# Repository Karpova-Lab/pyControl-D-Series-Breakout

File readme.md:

- View documentation at  https://karpova-lab.github.io/pyControl-D-Series-Breakout/
- Ask questions at https://github.com/Karpova-Lab/pyControl-D-series-Breakout/discussions
- Clone repository from https://github.com/Karpova-Lab/pyControl-D-Series-Breakout

## License
This project is licensed under the [Janelia open-source hardware license](license_hardare.txt) and [Janelia 3-term BSD open-source software license](license_software.txt).

Please contact [innovation@janelia.hhmi.org](mailto:innovation@janelia.hhmi.org) if you have any questions about licensing or would like to use this project commercially.

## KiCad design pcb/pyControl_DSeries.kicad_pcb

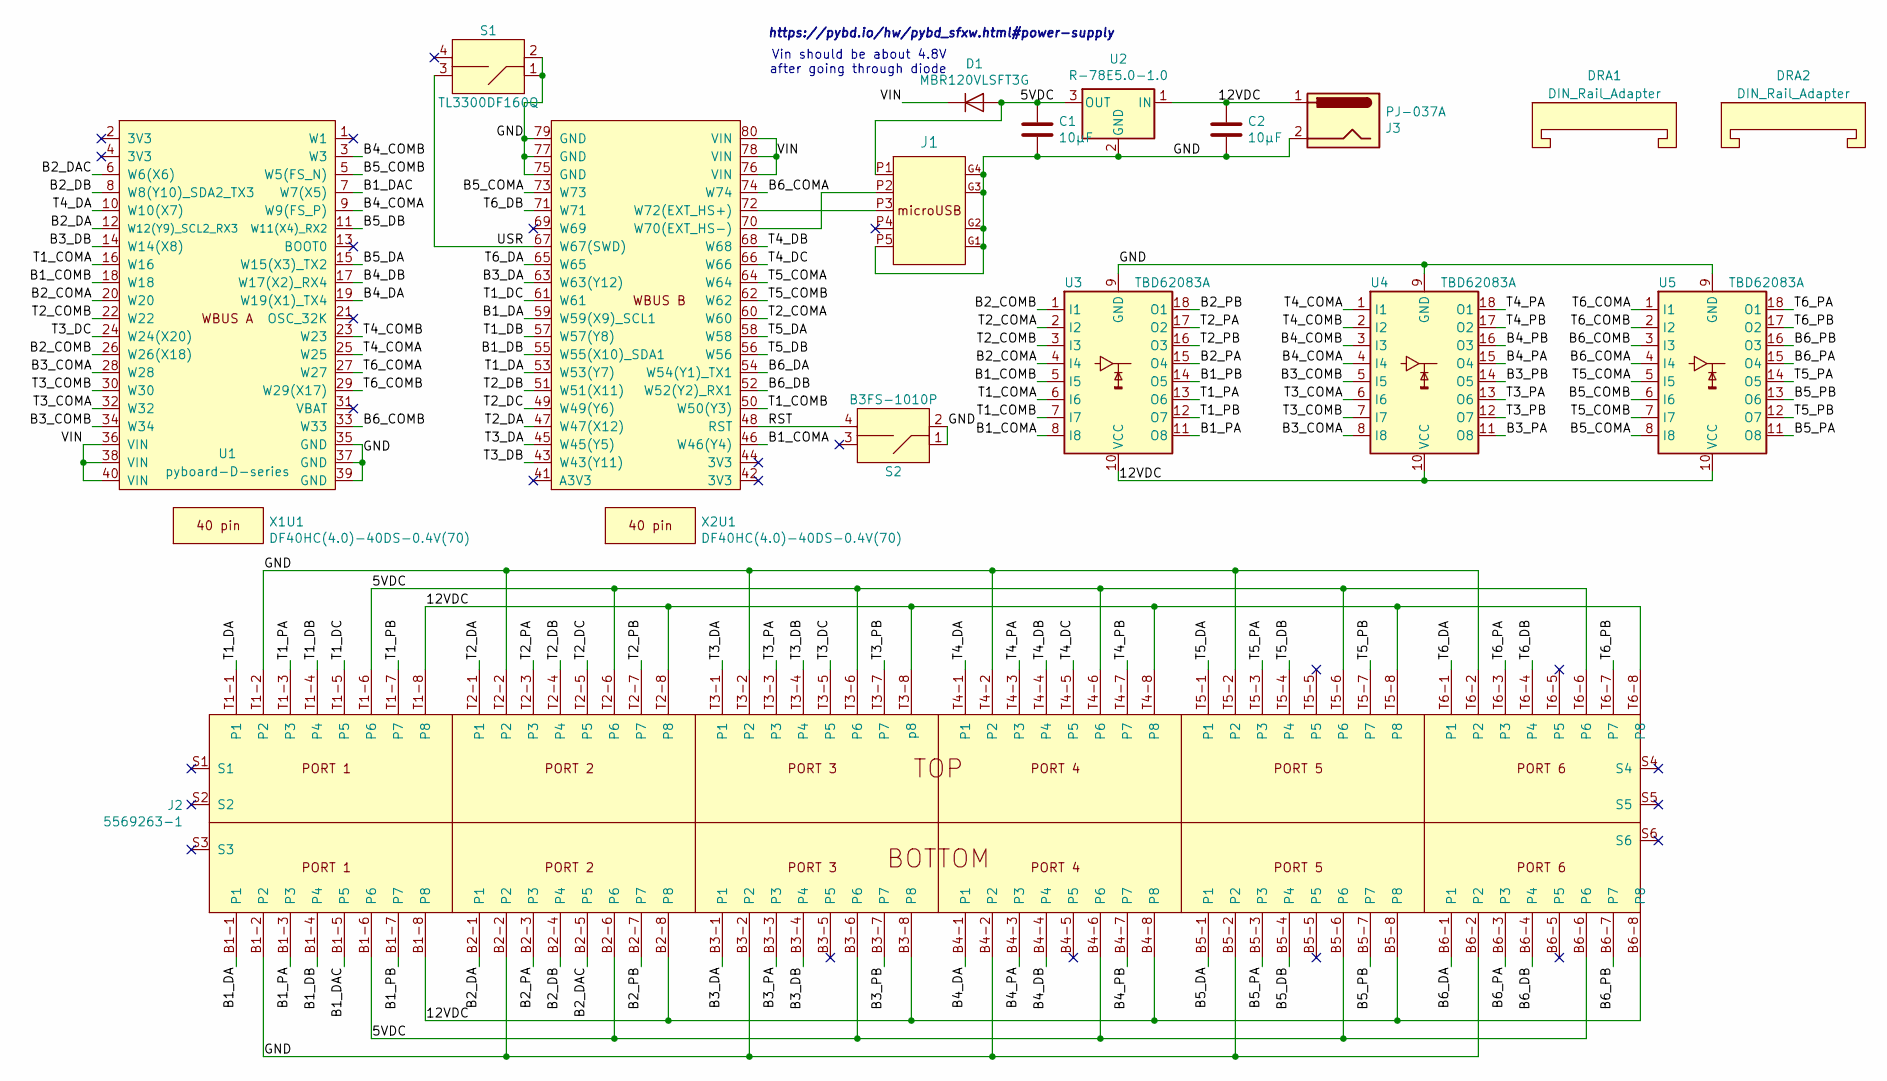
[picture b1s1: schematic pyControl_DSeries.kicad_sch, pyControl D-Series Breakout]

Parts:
C1, C2: 10µF; C_1206_3216Metric
D1: MBR120VLSFT3G; D_SOD-123F
DRA1, DRA2: DIN_Rail_Adapter; DIN_Clip
J1: 10118194-0001LF; microUSB_horizontal_socket
J2: 5569263-1; RJ45_12Port
J3: PJ-037A; DC_Jack
S1: TL3300DF160Q; 12mm_tactile_smd
S2: B3FS-1010P; 6mm_tactile_smd
U1: pyboard-D-series; PyBoard_D-Series
U2: R-78E5.0-1.0; Converter_DCDC_RECOM_R-78E-0.5_THT
U3, U4, U5: TBD62083A; SSOP-18_4.4x6.5mm_P0.65mm
X1U1, X2U1: DF40HC(4.0)-40DS-0.4V(70); Hirose_40_pin

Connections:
/5VDC: C1.1, D1.2 (A), J1.P1, J2.B1-6 (P6), J2.B2-6 (P6), J2.B3-6 (P6), J2.B4-6 (P6), J2.B5-6 (P6), J2.B6-6 (P6), J2.T1-6 (P6), J2.T2-6 (P6), J2.T3-6 (P6), J2.T4-6 (P6), J2.T5-6 (P6), J2.T6-6 (P6), U2.3 (OUT)
/12VDC: C2.1, J2.B1-8 (P8), J2.B2-8 (P8), J2.B3-8 (P8), J2.B4-8 (P8), J2.B5-8 (P8), J2.B6-8 (P8), J2.T1-8 (P8), J2.T2-8 (P8), J2.T3-8 (p8), J2.T4-8 (P8), J2.T5-8 (P8), J2.T6-8 (P8), J3.1, U2.1 (IN), U3.10 (VCC), U4.10 (VCC), U5.10 (VCC)
/B1_COMA: U1.46 (W46(Y4)), U3.8 (I8)
/B1_COMB: U1.18 (W18), U3.5 (I5)
/B1_DA: J2.B1-1 (P1), U1.59 (W59(X9)_SCL1)
/B1_DAC: J2.B1-5 (P5), U1.7 (W7(X5))
/B1_DB: J2.B1-4 (P4), U1.55 (W55(X10)_SDA1)
/B1_PA: J2.B1-3 (P3), U3.11 (O8)
/B1_PB: J2.B1-7 (P7), U3.14 (O5)
/B2_COMA: U1.20 (W20), U3.4 (I4)
/B2_COMB: U1.26 (W26(X18)), U3.1 (I1)
/B2_DA: J2.B2-1 (P1), U1.12 (W12(Y9)_SCL2_RX3)
/B2_DAC: J2.B2-5 (P5), U1.6 (W6(X6))
/B2_DB: J2.B2-4 (P4), U1.8 (W8(Y10)_SDA2_TX3)
/B2_PA: J2.B2-3 (P3), U3.15 (O4)
/B2_PB: J2.B2-7 (P7), U3.18 (O1)
/B3_COMA: U1.28 (W28), U4.8 (I8)
/B3_COMB: U1.34 (W34), U4.5 (I5)
/B3_DA: J2.B3-1 (P1), U1.63 (W63(Y12))
/B3_DB: J2.B3-4 (P4), U1.14 (W14(X8))
/B3_PA: J2.B3-3 (P3), U4.11 (O8)
/B3_PB: J2.B3-7 (P7), U4.14 (O5)
/B4_COMA: U1.9 (W9(FS_P)), U4.4 (I4)
/B4_COMB: U1.3 (W3), U4.3 (I3)
/B4_DA: J2.B4-1 (P1), U1.19 (W19(X1)_TX4)
/B4_DB: J2.B4-4 (P4), U1.17 (W17(X2)_RX4)
/B4_PA: J2.B4-3 (P3), U4.15 (O4)
/B4_PB: J2.B4-7 (P7), U4.16 (O3)
/B5_COMA: U1.73 (W73), U5.8 (I8)
/B5_COMB: U1.5 (W5(FS_N)), U5.6 (I6)
/B5_DA: J2.B5-1 (P1), U1.15 (W15(X3)_TX2)
/B5_DB: J2.B5-4 (P4), U1.11 (W11(X4)_RX2)
/B5_PA: J2.B5-3 (P3), U5.11 (O8)
/B5_PB: J2.B5-7 (P7), U5.13 (O6)
/B6_COMA: U1.74 (W74), U5.4 (I4)
/B6_COMB: U1.33 (W33), U5.3 (I3)
/B6_DA: J2.B6-1 (P1), U1.54 (W54(Y1)_TX1)
/B6_DB: J2.B6-4 (P4), U1.52 (W52(Y2)_RX1)
/B6_PA: J2.B6-3 (P3), U5.15 (O4)
/B6_PB: J2.B6-7 (P7), U5.16 (O3)
/GND: C1.2, C2.2, J1.G1, J1.G2, J1.G3, J1.G4, J1.P5, J2.B1-2 (P2), J2.B2-2 (P2), J2.B3-2 (P2), J2.B4-2 (P2), J2.B5-2 (P2), J2.B6-2 (P2), J2.T1-2 (P2), J2.T2-2 (P2), J2.T3-2 (P2), J2.T4-2 (P2), J2.T5-2 (P2), J2.T6-2 (P2), J3.2, S1.1 (in1), S1.2 (in2), S2.1 (in1), S2.2 (in2), U1.35 (GND), U1.37 (GND), U1.39 (GND), U1.75 (GND), U1.77 (GND), U1.79 (GND), U2.2 (GND), U3.9 (GND), U4.9 (GND), U5.9 (GND)
/RST: S2.4 (out2), U1.48 (RST)
/T1_COMA: U1.16 (W16), U3.6 (I6)
/T1_COMB: U1.50 (W50(Y3)), U3.7 (I7)
/T1_DA: J2.T1-1 (P1), U1.53 (W53(Y7))
/T1_DB: J2.T1-4 (P4), U1.57 (W57(Y8))
/T1_DC: J2.T1-5 (P5), U1.61 (W61)
/T1_PA: J2.T1-3 (P3), U3.13 (O6)
/T1_PB: J2.T1-7 (P7), U3.12 (O7)
/T2_COMA: U1.60 (W60), U3.2 (I2)
/T2_COMB: U1.22 (W22), U3.3 (I3)
/T2_DA: J2.T2-1 (P1), U1.47 (W47(X12))
/T2_DB: J2.T2-4 (P4), U1.51 (W51(X11))
/T2_DC: J2.T2-5 (P5), U1.49 (W49(Y6))
/T2_PA: J2.T2-3 (P3), U3.17 (O2)
/T2_PB: J2.T2-7 (P7), U3.16 (O3)
/T3_COMA: U1.32 (W32), U4.6 (I6)
/T3_COMB: U1.30 (W30), U4.7 (I7)
/T3_DA: J2.T3-1 (P1), U1.45 (W45(Y5))
/T3_DB: J2.T3-4 (P4), U1.43 (W43(Y11))
/T3_DC: J2.T3-5 (P5), U1.24 (W24(X20))
/T3_PA: J2.T3-3 (P3), U4.13 (O6)
/T3_PB: J2.T3-7 (P7), U4.12 (O7)
/T4_COMA: U1.25 (W25), U4.1 (I1)
/T4_COMB: U1.23 (W23), U4.2 (I2)
/T4_DA: J2.T4-1 (P1), U1.10 (W10(X7))
/T4_DB: J2.T4-4 (P4), U1.68 (W68)
/T4_DC: J2.T4-5 (P5), U1.66 (W66)
/T4_PA: J2.T4-3 (P3), U4.18 (O1)
/T4_PB: J2.T4-7 (P7), U4.17 (O2)
/T5_COMA: U1.64 (W64), U5.5 (I5)
/T5_COMB: U1.62 (W62), U5.7 (I7)
/T5_DA: J2.T5-1 (P1), U1.58 (W58)
/T5_DB: J2.T5-4 (P4), U1.56 (W56)
/T5_PA: J2.T5-3 (P3), U5.14 (O5)
/T5_PB: J2.T5-7 (P7), U5.12 (O7)
/T6_COMA: U1.27 (W27), U5.1 (I1)
/T6_COMB: U1.29 (W29(X17)), U5.2 (I2)
/T6_DA: J2.T6-1 (P1), U1.65 (W65)
/T6_DB: J2.T6-4 (P4), U1.71 (W71)
/T6_PA: J2.T6-3 (P3), U5.18 (O1)
/T6_PB: J2.T6-7 (P7), U5.17 (O2)
/USR: S1.3 (out1), U1.67 (W67(SWD))
/VIN: D1.1 (K), U1.36 (VIN), U1.38 (VIN), U1.40 (VIN), U1.76 (VIN), U1.78 (VIN), U1.80 (VIN)
unnamed: J1.P2, U1.70 (W70(EXT_HS-))
unnamed: J1.P3, U1.72 (W72(EXT_HS+))

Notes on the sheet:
https://pybd.io/hw/pybd_sfxw.html#power-supply
Vin should be about 4.8V after going through diode

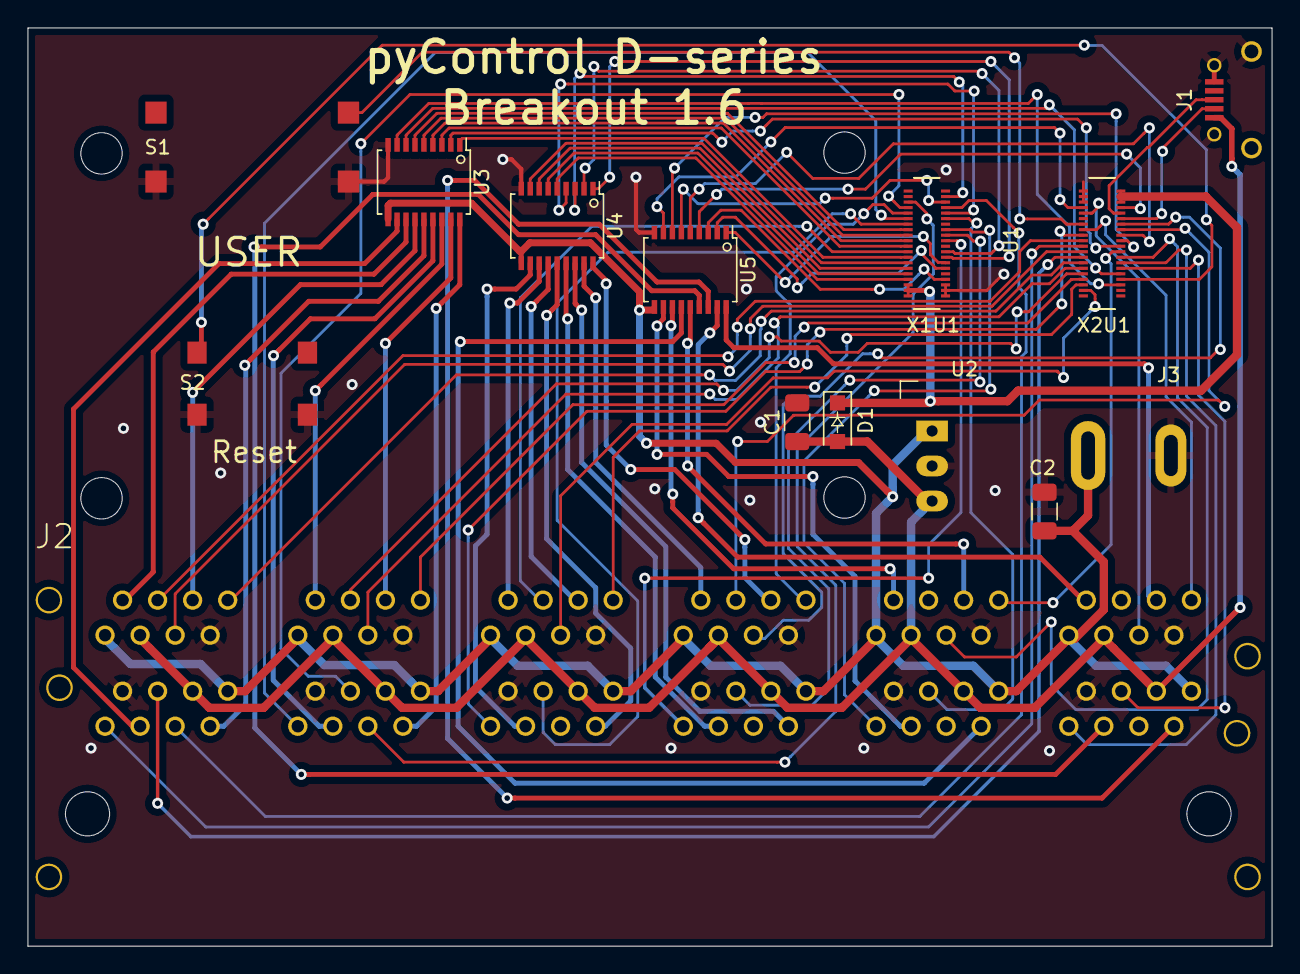
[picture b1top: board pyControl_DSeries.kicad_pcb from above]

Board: 2 copper layers, 90.2 x 66.5 mm, 17 parts (0 on the bottom side), 86 nets.

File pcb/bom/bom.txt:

"Qty","Reference","Description","Value/MPN","Purchase Link"
"2","C2, C1","1206 Capacitor","10µF","https://www.digikey.com/products/en?keywords=1276-1804-1-ND"
"1","D1","Schottky Diode","MBR120VLSFT3G","https://www.digikey.com/products/en?keywords=MBR120VLSFT3GOSCT-ND"
"1","J1","Micro USB Socket","10118194-0001LF","https://www.digikey.com/products/en?keywords=609-4618-1-ND"
"1","J2","12-port RJ45 Connector","5569263-1","https://www.digikey.com/products/en?keywords=5569263"
"1","J3","Barrel Jack Connector","PJ-037A","https://www.digikey.com/product-detail/en/cui-inc/PJ-037A/CP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"
"1","S1","Large Tactile Switch","TL3300DF160Q","https://www.digikey.com/products/en?keywords=EG4906CT-ND"
"1","S2","Small Tactile Switch","B3FS-1010P","https://www.digikey.com/products/en?keywords=sw1440ct"
"1","U2","5V DC to DC Converter","R-78E5.0-1.0","https://www.digikey.com/products/en?keywords=945-2201-ND"
"3","U5, U4, U3","8-channel Driver Array","TBD62083A","https://www.digikey.com/products/en?keywords=TBD62083AFNGELCT-ND"
"2","X2U1, X1U1","40-pin Connector","DF40HC(4.0)-40DS-0.4V(70)","https://www.digikey.com/products/en?keywords=H124604CT-ND"

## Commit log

2019-04-12 Initial commit. v1.0
2019-04-24 rev 1.1 fixed pins on dc jack and linear regulator. connected T3_DC repositioned DIN adapters added BOM and datasheets
2019-05-07 made footprint and symbol libraries local to project
2019-05-07 rough draft of documentation added
2019-05-07 renamed docs_content to doc_content
2019-05-09 pcb libraries are now a git submodule
2019-05-09 another doc rename
2019-05-09 added license and readme
2019-05-09 Revised PCB to v1.2 Switched from linear regulator to DC-DC converter. 1µF capacitors are now 10µF. Added TAPR link to silkscreen and schematic.
2019-05-13 Doc update
2019-07-26 pcb version 1.3. W1 cannot be used as DIO, so now B4_COMA is connected to pin9 (W9). W69 cannot be used as DIO, so now B5_COMB is connected to pin5 (W5). Added microusb connector so that you can perm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
2019-07-26 updated docs for v1.3
2019-07-26 micro usb socket was missing from docs
2019-07-29 Doc update. Added more resource links. Comparison now uses highest tier d-series board PYBD-SF6-W4F2
2019-08-05 PCB rev 1.4 removed mounting pads from D40 Hirose connector since that version of connector is discontinued. shifted pyboard connectors down and to the left so now an SD card can be inserted without 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
2019-08-05 Doc cleanup
2019-08-20 merged docs into one page
2019-09-05 fixed typo and broken link
2019-10-17 readme and docs update
2019-10-17 pcb v1.5. Rearranged pins to jack mapping.
    To get top row inputs on separate interrupt vectors
    T3_C was W74, now Q24
    T4_B was W62, now W68
    T4_C was W60, now W66
    T6_A was W50, now W65
    T6_A was W46, now W71
2019-10-17 fixed typos in docs
2019-10-29 updated device file
2020-04-02 pcb v1.6. new rj45 footprint. swapped W49 and W51 so now interrupt vector 13 is on DIO_C of port 2. can have entire row of DIO-A and DIO-B interrupts without collisions
2021-03-02 Doc update
    - added notes about SPI and interrupt vectors
    - fixed pinout diagram. Port 2 DIO_B and DIO_C were swapped.
2021-03-03 Added benchmarking data and analysis
2021-03-03 performance comparison documentation update
2021-03-03 fixed wording
2021-03-03 added % < 1ms to documentation
2021-03-03 fixed broken osh park image link
2021-04-26 Fixed SPI port spreadsheet and other doc cleanup
    A mistake in the pinout diagram was corrected in commit bf2bec864f299681884a0b370ce6527de034c568 however the SPI port spreadsheet did not reflect the change.
    spreadsheet updates:
    - SCK for SPI(2) was Port2B, now corrected to Port2C
    - fixed broken link to D-series pinouts.jpg
    other updates:
    - added labeled diagram to overview page
2021-04-26 added labeled diagram to readme
2021-05-05 foundation for hugo docs
2021-05-14 Change from sphinx docs to Hugo docs
2021-05-14 fixed broken image links
2021-05-15 fixed broken download link
2021-05-17 updated some doc images
2021-05-19 doc css adjustments
2021-05-28 doc theme update
2021-06-08 doc updates
2021-06-25 fixed broken link to lever project
2021-08-18 readme update
2022-03-22 update PCB files to KiCad v6
2022-03-22 migrated docs from hugo to mkdocs
2022-03-22 fix broken readme picture links
2022-03-31 "using" page doc updates
    - cleaned up HS USB setup
    - SPI chip select should not be rigidly specified. Removed from table.
2022-06-10 better doc page navigation
2022-06-11 removed text that was getting cutoff
2022-11-30 temp
2023-08-16 updated doc libraries
2024-12-29 updated benchmarks and docs
2024-12-29 fix missing logo and css
2025-09-05 license update

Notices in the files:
pcb/pyControl_DSeries.kicad_sch:
Licensed under the TAPR Open Hardware License (www.tapr.org/OHL)
